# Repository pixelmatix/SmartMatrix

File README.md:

# SmartMatrix Library for Teensy 3, Teensy 4, and ESP32

SmartMatrix Library is designed to refresh HUB75 LED matrix panels and APA102-compatible addressable LEDs with high quality graphics, using simple Arduino sketches.

<p align="center"><i>128x64 HUB75 Panel Driven with SmartLED Shield for Teensy 4</i></p>

SmartMatrix Library 4 has support for Teensy 4.1, Teensy 4.0, Teensy 3.6, Teensy 3.5, Teensy 3.2/3.1, Teensy 3.0, as well as experimental support for ESP32.

The code to refresh HUB75 panels takes advantage of platform-specific peripherals like DMA, I2S, FlexIO, and once started runs in the background using interrupts. It takes a lot of work to port SmartMatrix Library to a new platform. We're working on an open source solution that will allow a lot more platforms to drive HUB75 panels, [sign up for updates here](https://github.com/pixelmatix/SmartMatrix/issues/131) if you're interested.

The documentation in this README contains the basic information you may need to run your first SmartMatrix Library sketch, but there is more detailed documentation in the [SmartMatrix Wiki](https://github.com/pixelmatix/SmartMatrix/wiki).

## Hardware

SmartMatrix Library runs best on the Teensy 4.0 and 4.1 using the SmartLED Shield for Teensy 4, available from [distributors in the US and China](http://docs.pixelmatix.com/SmartMatrix/shop.html). If you want to use the less powerful but more mature Teensy 3, you can use the SmartLED Shield for Teensy 3, available from [Adafruit](https://www.adafruit.com/product/1902), [SparkFun](http://sparkfun.com/products/15046), [Digi-Key](https://www.digikey.com/product-detail/en/sparkfun-electronics/DEV-15046/1568-1954-ND/9739875), and other distributors around the globe. The shield doesn't require any soldering to get started, besides putting pins on your Teensy board.

<p align="center"><i>SmartLED Shield for Teensy 3 - Photo Courtesy Adafruit</i></p>

There's an [adapter PCB design](https://community.pixelmatix.com/t/teensy-4-0-released/498/32) to upgrade SmartLED Shield for Teensy 3 to work with the Teensy 4.

You can wire up a [bare Teensy 3.x to a HUB75 panel](http://docs.pixelmatix.com/SmartMatrix/shieldref.html#smartled-shield-formerly-smartmatrix-shield-overview-technical-details-manually-connecting-teensy-and-panel), but at a minimum it's recommended to use 5V level shifters to drive the panels with the voltage level they are expecting. There's a recommended circuit with latch chip to use with the Teensy 3 that will reduce the amount of pins used. The Teensy 4 requires an external latch.

The shields are Open Source Hardware, with design files posted in the `/extras/hardware/` directories.

Documentation for the SmartLED Shield Hardware is available here: [SmartMatrix Docs](http://docs.pixelmatix.com/SmartMatrix/shieldref.html)

## Teensy 4

Teensy 4 support was contributed by [Eric Eason](https://github.com/easone)

Teensy 4 APA102 support depends on FlexIO_t4 by KurtE, which is included as a submodule in `src/lib/`. The original FlexIO_t4 library is [on GitHub](https://github.com/KurtE/FlexIO_t4)

## ESP32

The ESP32 platform is supported with SmartMatrix Library 4.0, but not all features are up to par with the Teensy 3/4 ports. For details on the ESP32 port, see the [Wiki][def]

## Changes from SmartMatrix Library 3.x

- Sketches written for SmartMatrix Library 3.x should work with SmartMatrix Library 4.0 with a few changes.
- See MIGRATION.md for details on how to update your SmartMatrix Library 3.x sketches for SmartMatrix Library 4.x
- A lot of files were subtly renamed, just changing the case. If you're trying to use git to check out a commit and get an error like `The following untracked working tree files would be overwritten by checkout`, you may need to use git from the command line and add the `-f` parameter to force checkout (throwaway local modifications), as your git client might think it's overwriting the case-changed files and losing data.

### New Features in SmartMatrix Library 4.0

- Support for Teensy 4 and ESP32
- Support for driving APA102 LEDs on Teensy platforms
- New "GFX" layers rewritten for better efficiency, and using Adafruit_GFX for drawing, fonts, including much larger fonts
- Support for panels with non-standard mapping, e.g. 16x32/4 (MOD4) panels
- See more features in the [SmartMatrix Wiki](https://github.com/pixelmatix/SmartMatrix/wiki)

## HUB75 Panels

HUB75 RGB panels are typically used for LED billboards (e.g. Times Square), making them cost-effective and readily available. They’re much cheaper per-pixel than addressable LEDs, and available in a wide range of pixel pitch (as of now, 2 mm spacing up to 10 mm spacing per LED). They do require an external controller to continually send data to the panels to refresh them line by line, and that’s where the SmartLED Shield and SmartMatrix library come in. Adafruit, Sparkfun, and other distributors carry panels that are known to be compatible with SmartLED Shield and the SmartMatrix library, but most panels on AliExpress and other sources are compatible as well.

The pixel pitch and "RGB" are good search terms on Aliexpress, e.g. "P6 RGB" for a 6 mm pitch RGB HUB75 panel.

<p align="center"><i>HUB75 Panels Ranging from P2 to P10 pitch</i></p>

## Getting Started

To download in Arduino Library form, see [Releases](https://github.com/pixelmatix/SmartMatrix/releases) on GitHub, or use Arduino Library Manager.

### Software and Teensy Setup

This documentation assumes you have a general knowledge of the Teensy 3 or Teensy 4, how to use the Arduino IDE, and the Teensyduino addon. If you need an overview of any of those tools, please use these references:

- [PJRC - Teensyduino](http://www.pjrc.com/teensy/teensyduino.html)
- [Arduino - Getting Started with Arduino](http://arduino.cc/en/Guide/HomePage)
- For general Teensy support, not related to the SmartMatrix Shield or SmartMatrix Library, post a question at the [PJRC Forum](http://forum.pjrc.com/forums/3-Technical-Support-amp-Questions)

Make sure you have a supported version of the Arduino IDE and Teensyduino add-on installed.

- [Arduino IDE](http://arduino.cc/en/main/software) - version 1.6.5 or later recommended
- [Teensyduino](http://www.pjrc.com/teensy/td_download.html) - use the latest version

Before continuing, use the blink example in the Arduino IDE to verify you can compile and run a sketch on your Teensy 3.1/3.2.

Download the latest version of the SmartMatrix Library, or install it from Arduino Library Manager:  
[SmartMatrix Releases - GitHub](https://github.com/pixelmatix/SmartMatrix/releases)

Note: "SmartMatrix" Library used to be listed in Arduino Library Manager under "SmartMatrix3". You may need to look for the library in Arduino Library Manager or your libraries folder under either "SmartMatrix" or "SmartMatrix3" as we transition to the new name.

If you're not using Arduino Library Manager, you need to import the library into Arduino, see instructions from Arduino here:  
[Arduino - Libraries](http://arduino.cc/en/Guide/Libraries)

Some of the examples depend on other libraries, which you can download separately, or install from Arduino Library Manager. See "External Libraries" below.

Start with the FeatureDemo Example project, included with the library. From the Arduino File menu, choose Examples, SmartMatrix3 (or SmartMatrix), then FeatureDemo.

Find the section at the top with the note `// uncomment one line to select your MatrixHardware configuration`, and uncomment the file appropriate for your hardware.

You should already have most of the correct Arduino settings to load the FeatureDemo sketch on your Teensy, from running the blink example earlier. For Teensy 3: under Tools, CPU Speed, make sure either 48 MHz or 96MHz (overclock) is selected. (Some libraries are not compatible with the 72MHz CPU). For Teensy 4, use the default CPU speed.

The examples are configured to run on a 32x32-pixel panel. If your resolution is different, adjust the `kMatrixWidth` and `kMatrixHeight` variables at the top of the sketch. You may also need to change `kPanelType`. Some common kPanelType settings:

- 32-pixel high panels, e.g. 32x32, 64x32: `SM_PANELTYPE_HUB75_32ROW_MOD16SCAN`
- 16-pixel high panels, e.g. 32x16: `SMARTMATRIX_HUB75_16ROW_MOD8SCAN`
- 64-pixel high panels, e.g. 64x64, 128x64: `SM_PANELTYPE_HUB75_64ROW_MOD32SCAN`
- For other less common panels, see more details in `MatrixCommonHub75.h` and [the wiki]https://github.com/pixelmatix/SmartMatrix/wiki)

You can chain several panels together to create a wider or taller display than one panel would allow. Set `kMatrixWidth` and `kMatrixHeight` to the overall width and height of your display. If your display is more than one panel high, set `kMatrixOptions` to how you tiled your panels:

- Panel Order - By default, the first panel of each row starts on the same side, so you need a long ribbon cable to go from the last panel of the previous row to the first panel of the next row. `SM_HUB75_OPTIONS_C_SHAPE_STACKING` inverts the panel on each row to minimize the length of the cable going from the last panel of each row the first panel of the other row.
  - Note `SM_HUB75_OPTIONS_C_SHAPE_STACKING` isn't compatible with panels that require the Multi Row Refresh Mapping feature (if your `kPanelType` value includes the column size, it likely requires Multi Row Refresh Mapping, e.g. `SM_PANELTYPE_HUB75_16ROW_32COL_MOD2SCAN`)
- Panel Direction - By default the first panel is on the top row. To stack panels the other way, use `SM_HUB75_OPTIONS_BOTTOM_TO_TOP_STACKING`.
- To set multiple options, use the bitwise-OR operator e.g. for C-shape Bottom-to-top stacking: `const uint8_t kMatrixOptions = (SM_HUB75_OPTIONS_C_SHAPE_STACKING | SM_HUB75_OPTIONS_BOTTOM_TO_TOP_STACKING);`

Note: the stacking direction was reversed in the `teensylc` and `teensy4` branches prior to the release of SmartMatrix Library 4.0. The stacking direction is still reversed for the ESP32 Platform as of SmartMatrix Library 4.0.3, and will be fixed at some point in the future.

Click the Upload button, and the sketch should compile and upload to your Teensy, and start running right away.

You can use the FeatureDemo sketch (or other example sketches) as a way to get started with your own project. Inside `loop()`, find a demo section that is similar to what you want to do with your project, delete the other sections, and save it as as new sketch.

### External Libraries

Some SmartMatrix examples require external libraries to compile. You may already have older versions of these libraries installed in Arduino that may be too old to work with SmartMatrix and the examples. It's usually best to use [Arduino Library Manager](https://learn.adafruit.com/adafruit-all-about-arduino-libraries-install-use) and get the latest version of the library.

Installing Arduino libraries from GitHub has a couple pitfalls. [This Adafruit tutorial](https://learn.adafruit.com/adafruit-all-about-arduino-libraries-install-use/) explains the basics of installing libraries and how to avoid the pitfalls.

**GifDecoder and AnimatedGIF**

There are two libraries needed for the `AnimatedGifs` example. Both can be installed from Arduino Library Manager, or you can manually install from GitHub.

[GifDecoder](https://github.com/pixelmatix/GifDecoder/releases)

[AnimatedGIF](https://github.com/bitbank2/AnimatedGIF/releases)

**Adafruit_GFX**

You can optionally use Adafruit_GFX with SmartMatrix Library. The new "GFX" layers in SmartMatrix Library are much more efficient, and allow for using large fonts for both static display or scrolling across the screen.

Install Adafruit_GFX using Arduino Library Manager or manually [from GitHub](https://github.com/adafruit/Adafruit-GFX-Library/releases)

**FastLED**

If you're having trouble compiling sketches that use FastLED and are getting errors that refer to FastLED.h, try compiling the `FastLED_Functions` example first, which will help narrow down the issue. Also make sure you are using FastLED 3.1 or later.

This error means the FastLED library isn't installed (correctly):  
`fatal error: FastLED.h: No such file or directory`

The FastLED version included with Teensyduino may lag behind the latest. It's better to install FastLED manually using the latest version [available from GitHub](https://github.com/FastLED/FastLED/releases), or using Arduino Library Manager. If you see any of these errors, you likely have an older version of FastLED installed:  
`no known conversion for argument 4 from 'CRGB' to 'const rgb24&'`  
`error: 'inoise8' was not declared in this scope`

This can be tricky to track down as Teensyduino installs libraries into your Arduino application directory, which might not be in your Arduino sketchbook. Look at the `ResolveLibrary` messages you get when compiling to make sure that the version of library you want is being used.

You can manually install the latest version of FastLED (3.x or higher) from the FastLED releases page:
https://github.com/FastLED/FastLED/releases

**Teensy Audio Library**

The SpectrumAnalyzer sketches require the [Teensy Audio Library](http://www.pjrc.com/teensy/td_libs_Audio.html), which is included in Teensyduino. If you have trouble compiling, first make sure you can compile the `FastLED_Functions` example, as FastLED 3.x is also a requirement for this sketch. If you're missing the Audio library, the best way to install is by running the Teensyduino installer. Make sure the "Audio" library is checked during the install.

## Troubleshooting

If you need help, the best place to ask for help, or look for others who may have worked through the same issue, is the [SmartMatrix Community](https://community.pixelmatix.com). Please don't post troubleshooting requests here on GitHub.

If you've found a bug with the code, or want to suggest an improvement, feel free to submit a GitHub Issue or Pull Request.

## Supporting SmartMatrix Library Development

A lot of work went into writing SmartMatrix Library, designing the shields, and releasing them as Open Source Hardware. There are real costs in maintaining the documentation and community forum. If they are useful to you and you'd like to say thank you, you can make a [donation via PayPal](https://www.paypal.com/cgi-bin/webscr?cmd=_s-xclick&hosted_button_id=56RA5NKYXHCLJ&source=https://github.com/pixelmatix/SmartMatrix). Thank you!

[def]: https://github.com/pixelmatix/SmartMatrix/wiki/ESP32-Wiring

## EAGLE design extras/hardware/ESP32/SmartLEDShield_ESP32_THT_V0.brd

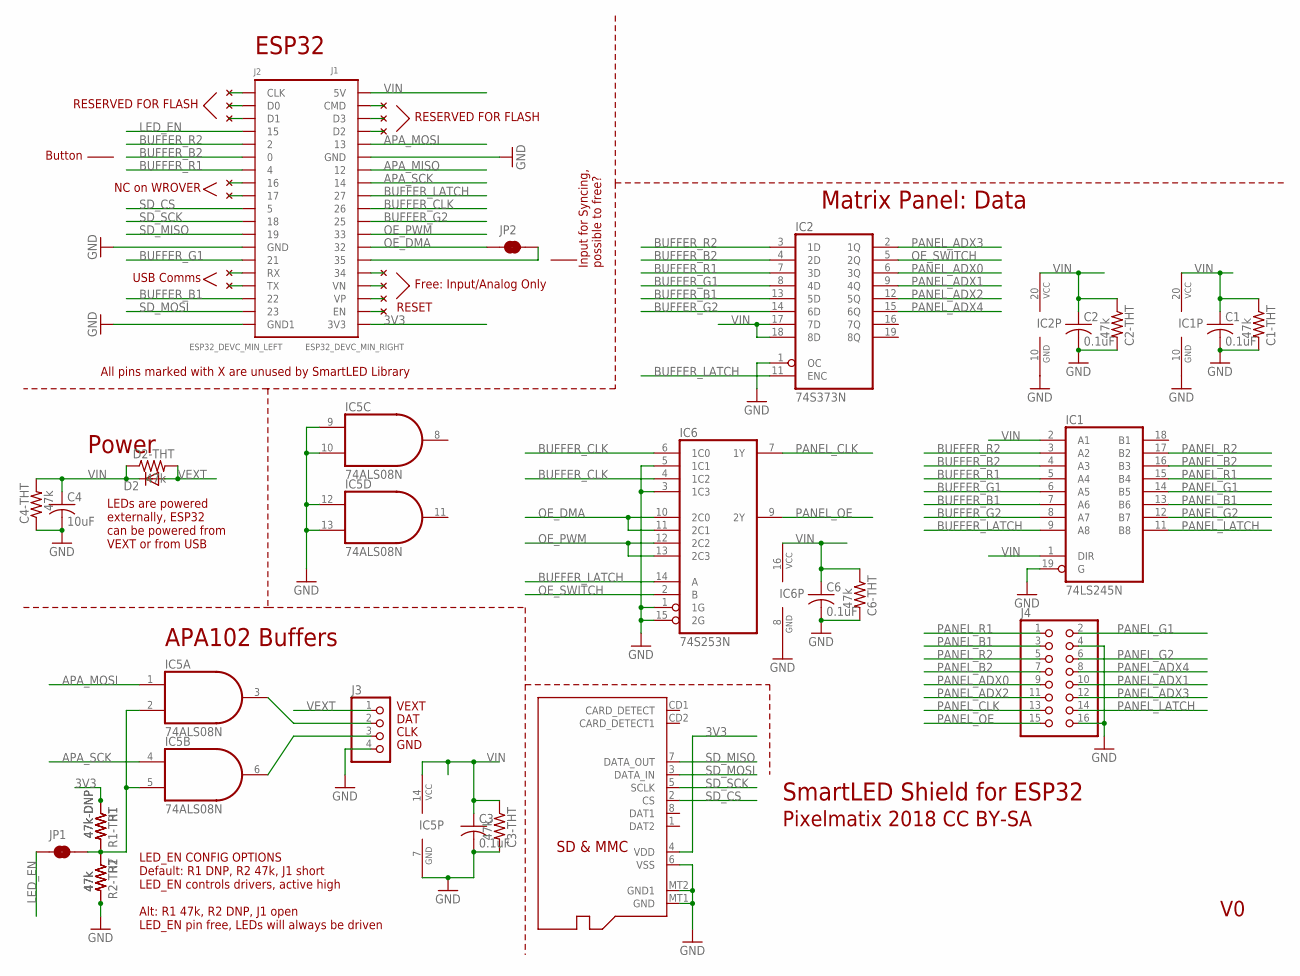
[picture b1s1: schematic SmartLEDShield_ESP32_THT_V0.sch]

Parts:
C1, C2, C3, C6: 0.1uF; C0603; PARTNO CAP CER 0.1UF 10V 10% X7R 0805
C1-THT, C2-THT, C3-THT, C4-THT, C6-THT: 47k; 0204/7
C4: 10uF; C0805; PARTNO CAP CER 0.1UF 10V 10% X7R 0805
D2: MBR1020VL; SOD123-FL
D2-THT: 47k; 0204/7
IC1: 74LS245N; DIL20
IC2: 74S373N; DIL20
IC5: 74ALS08N; DIL14
IC6: 74S253N; DIL16
J1: ESP32_DEVC_MIN_RIGHT; ESP32_DEVC_DUAL_HEADER_BOT_MOUNT_RIGHT
J2: ESP32_DEVC_MIN_LEFT; ESP32_DEVC_DUAL_HEADER_BOT_MOUNT_LEFT
J3: PINHD-1X04_2.54-S; 1X04-S
J4: PINHD-2X08_SMARTMATRIX_SSMTHT; SMARTMATRIX_SSMTHT
J6: MICROSD; PARTNO 101-00660-68-6
JP1, JP2: JUMPER-SMT_2_NC_TRACE_NO-SILK; SMT-JUMPER_2_NC_TRACE_NO-SILK
R1: 47k-DNP; R0603
R1-THT: 47k-DNP; 0204/7
R2: 47k; R0603
R2-THT: 47k; 0204/7

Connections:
3V3: J1.3V3A (3V3), J1.3V3B (3V3), J6.4 (VDD), R1.1, R1-THT.1
APA_MISO: J1.12A (12), J1.12B (12)
APA_MOSI: IC5.1 (I0), J1.13A_A (13), J1.13B_B (13)
APA_SCK: IC5.4 (I0), J1.14A_A (14), J1.14B_B (14)
BUFFER_B1: IC1.7 (A6), IC2.13 (5D), J2.22A (22), J2.22B (22)
BUFFER_B2: IC1.4 (A3), IC2.4 (2D), J2.0A (0), J2.0B (0)
BUFFER_CLK: IC6.4 (1C2), IC6.6 (1C0), J1.26A (26), J1.26B (26)
BUFFER_G1: IC1.6 (A5), IC2.8 (4D), J2.21A (21), J2.21B (21)
BUFFER_G2: IC1.8 (A7), IC2.14 (6D), J1.25A (25), J1.25B (25)
BUFFER_LATCH: IC1.9 (A8), IC2.11 (ENC), IC6.14 (A), J1.27A (27), J1.27B (27)
BUFFER_R1: IC1.5 (A4), IC2.7 (3D), J2.4A (4), J2.4B (4)
BUFFER_R2: IC1.3 (A2), IC2.3 (1D), J2.2A (2), J2.2B (2)
CLK1: IC5.6 (O), J3.3
DAT1: IC5.3 (O), J3.2
GND: C1.2, C1-THT.2, C2.2, C2-THT.2, C3.2, C3-THT.2, C4.2, C4-THT.1, C6.2, C6-THT.2, IC1.10 (GND), IC1.19 (G), IC2.1 (OC), IC2.10 (GND), IC5.7 (GND), IC5.9 (I0), IC5.10 (I1), IC5.12 (I0), IC5.13 (I1), IC6.1 (1G), IC6.3 (1C3), IC6.5 (1C1), IC6.8 (GND), IC6.15 (2G), J1.GNDA (GND), J1.GNDB (GND), J2.GND1A (GND1), J2.GND1B (GND1), J2.GNDA (GND), J2.GNDB (GND), J3.4, J4.4, J4.16, J6.6 (VSS), J6.MT1 (GND), J6.MT2 (GND1), R2.2, R2-THT.2
LED_EN: J2.15A_A (15), J2.15B_B (15), JP1.1
unnamed: J1.35A (35), J1.35B (35), JP2.2
unnamed: J1.CMD_A (CMD), J1.CMD_B (CMD)
unnamed: J1.D3_A (D3), J1.D3_B (D3)
unnamed: IC5.2 (I1), IC5.5 (I1), JP1.2, R1.2, R1-THT.2, R2.1, R2-THT.1
unnamed: J1.D2A (D2), J1.D2B (D2)
unnamed: J2.CLKA (CLK), J2.CLKB (CLK)
unnamed: J2.D0A (D0), J2.D0B (D0)
unnamed: J2.D1A (D1), J2.D1B (D1)
unnamed: J1.VNA (VN), J1.VNB (VN)
unnamed: J1.VPA (VP), J1.VPB (VP)
unnamed: J1.34A (34), J1.34B (34)
unnamed: J1.ENA (EN), J1.ENB (EN)
unnamed: J2.TXA (TX), J2.TXB (TX)
unnamed: J2.RXA (RX), J2.RXB (RX)
unnamed: J2.17A_A (17), J2.17B_B (17)
unnamed: J2.16A_A (16), J2.16_B (16)
OE_DMA: IC6.10 (2C0), IC6.11 (2C1), J1.32A (32), J1.32B (32), JP2.1
OE_PWM: IC6.12 (2C2), IC6.13 (2C3), J1.33A (33), J1.33B (33)
OE_SWITCH: IC2.5 (2Q), IC6.2 (B)
PANEL_ADX0: IC2.6 (3Q), J4.9
PANEL_ADX1: IC2.9 (4Q), J4.10
PANEL_ADX2: IC2.12 (5Q), J4.11
PANEL_ADX3: IC2.2 (1Q), J4.12
PANEL_ADX4: IC2.15 (6Q), J4.8
PANEL_B1: IC1.13 (B6), J4.3
PANEL_B2: IC1.16 (B3), J4.7
PANEL_CLK: IC6.7 (1Y), J4.13
PANEL_G1: IC1.14 (B5), J4.2
PANEL_G2: IC1.12 (B7), J4.6
PANEL_LATCH: IC1.11 (B8), J4.14
PANEL_OE: IC6.9 (2Y), J4.15
PANEL_R1: IC1.15 (B4), J4.1
PANEL_R2: IC1.17 (B2), J4.5
SD_CS: J2.5A (5), J2.5B (5), J6.2 (CS)
SD_MISO: J2.19A_A (19), J2.19B_B (19), J6.7 (DATA_OUT)
SD_MOSI: J2.23A (23), J2.23B (23), J6.3 (DATA_IN)
SD_SCK: J2.18A_A (18), J2.18B_B (18), J6.5 (SCLK)
VEXT: D2.A, D2-THT.2, J3.1
VIN: C1.1, C1-THT.1, C2.1, C2-THT.1, C3.1, C3-THT.1, C4.1, C4-THT.2, C6.1, C6-THT.1, D2.C, D2-THT.1, IC1.1 (DIR), IC1.2 (A1), IC1.20 (VCC), IC2.17 (7D), IC2.18 (8D), IC2.20 (VCC), IC5.14 (VCC), IC6.16 (VCC), J1.5V_A (5V), J1.5V_B (5V)

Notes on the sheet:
SmartLED Shield for ESP32
Pixelmatix 2018 CC BY-SA
ESP32
Matrix Panel: Data
VEXT
CLK
GND
DAT
Power
LEDs are powered externally, ESP32 can be powered from VEXT or from USB
LED_EN CONFIG OPTIONS Default: R1 DNP, R2 47k, J1 short LED_EN controls drivers, active high Alt: R1 47k, R2 DNP, J1 open LED_EN pin free, LEDs will always be driven
APA102 Buffers
All pins marked with X are unused by SmartLED Library
RESERVED FOR FLASH
Free: Input/Analog Only
Input for Syncing, possible to free?
RESET
USB Comms
NC on WROVER
Button

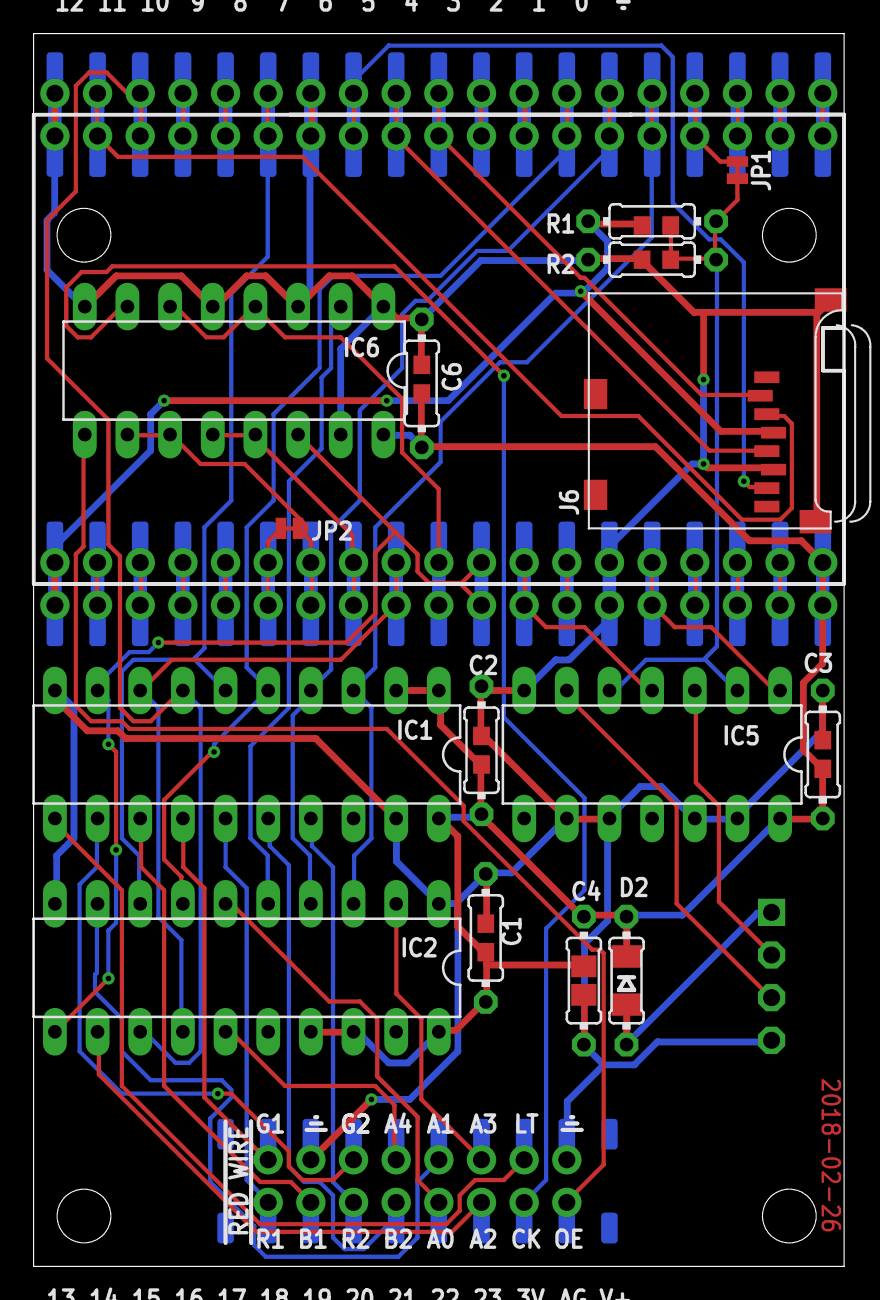
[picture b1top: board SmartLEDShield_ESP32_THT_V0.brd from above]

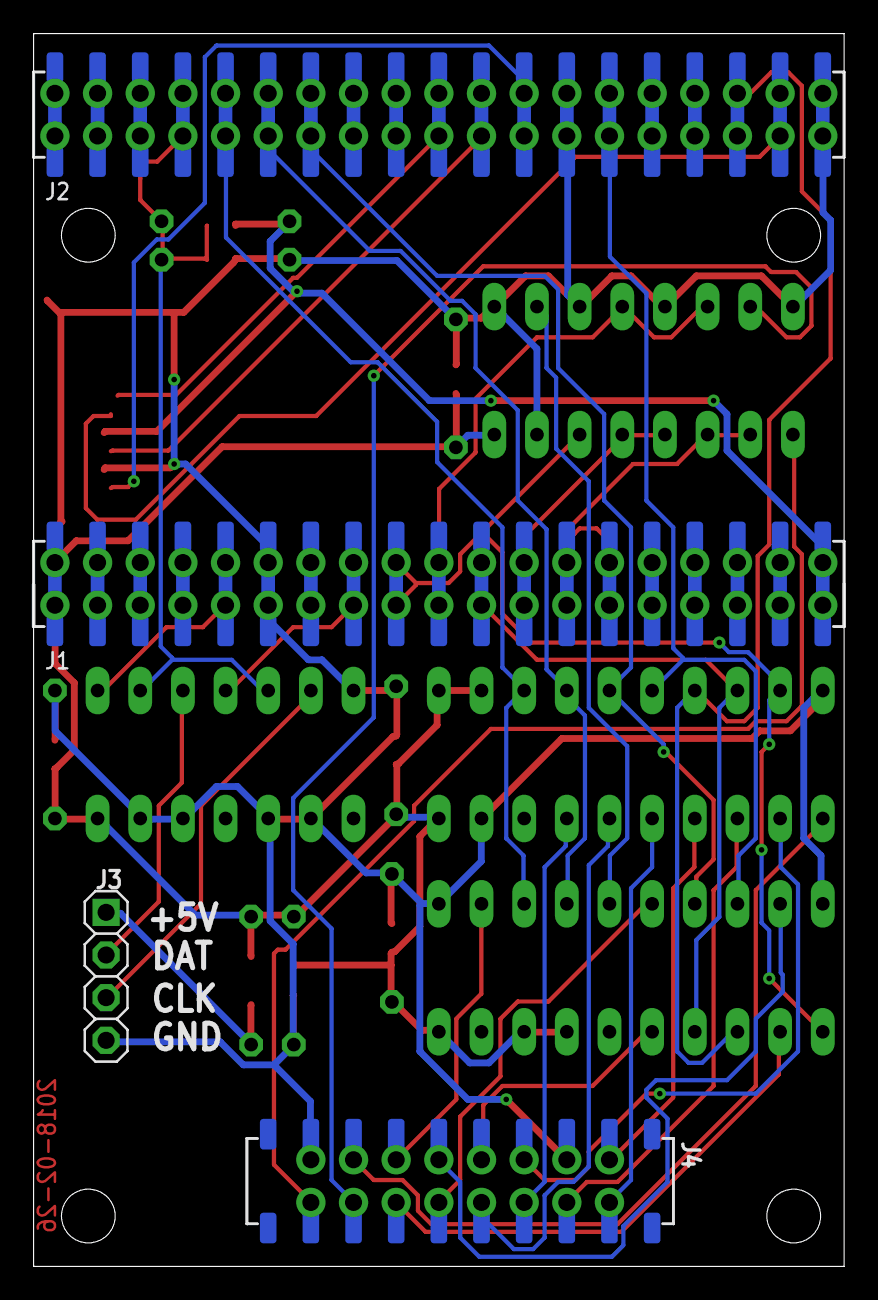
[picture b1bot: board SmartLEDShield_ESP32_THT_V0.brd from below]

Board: 2 copper layers, 48.3 x 73.4 mm, 31 parts (4 on the bottom side), 55 nets.

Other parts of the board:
H1, H3, H6, H9: STAND-OFFSTAND-OFF-3MM; STAND-OFF-3MM

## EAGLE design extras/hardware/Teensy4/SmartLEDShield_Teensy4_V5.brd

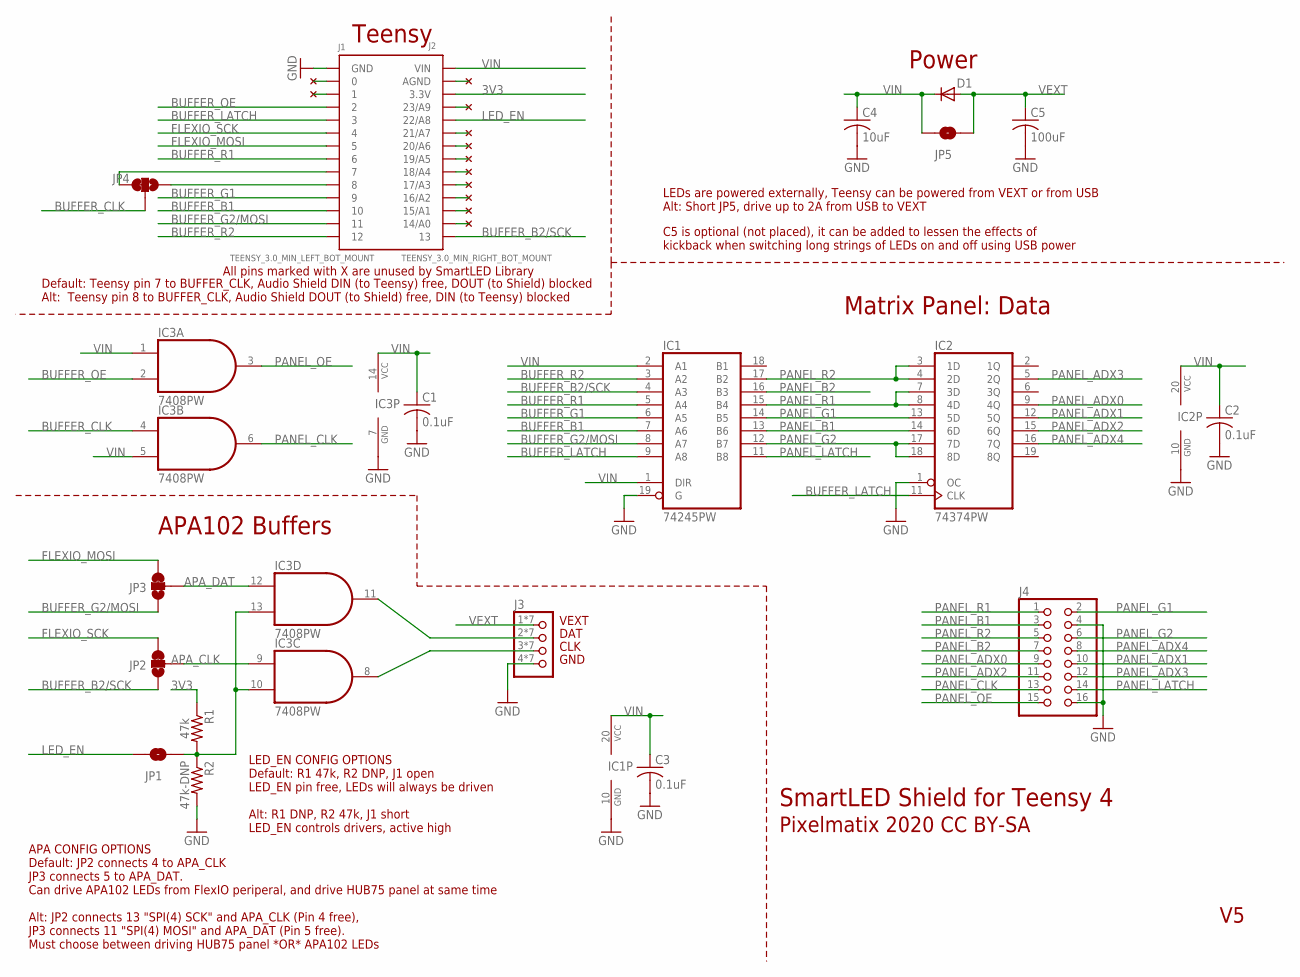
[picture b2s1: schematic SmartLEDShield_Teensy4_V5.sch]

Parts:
C1, C2, C3: 0.1uF; C0603; PARTNO CAP CER 0.1UF 10V 10% X7R 0805
C4: 10uF; C0805; PARTNO CAP CER 0.1UF 10V 10% X7R 0805
C5: 100uF; C1206; PARTNO CAP CER 0.1UF 10V 10% X7R 0805
D1: MBR0520LT; SOD123
IC1: 74245PW; TSSOP-20
IC2: 74374PW; TSSOP-20
IC3: 7408PW; TSSOP14
J1: TEENSY_3.0_MIN_LEFT_BOT_MOUNT; TEENSY_DUAL_HEADER_BOT_MOUNT_LEFT
J2: TEENSY_3.0_MIN_RIGHT_BOT_MOUNT; TEENSY_DUAL_HEADER_BOT_MOUNT_RIGHT
J3: PINHD-1X04_WIREPADS_NARROW; 1X04SMDWIRES_NARROW
J4: PINHD-2X08_SMARTMATRIX_SSMTHT; SMARTMATRIX_SSMTHT
JP1, JP5: JUMPER-SMT_2_NO_SILK; SMT-JUMPER_2_NO_SILK
JP2, JP3: JUMPER-SMT_3_1-NC_TRACE_SILK; SMT-JUMPER_3_1-NC_TRACE_SILK
JP4: JUMPER-SMT_3_1-NC_TRACE_NO-SILK; SMT-JUMPER_3_1-NC_TRACE_NO-SILK
R1: 47k; R0603
R2: 47k-DNP; R0603

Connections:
3V3: J2.3V3_A (3.3V), J2.3V3_B (3.3V), R1.1
APA_CLK: IC3.9 (I0), JP2.2
APA_DAT: IC3.12 (I0), JP3.2
BUFFER_B1: IC1.7 (A6), J1.10A (10), J1.10B (10)
BUFFER_B2/SCK: IC1.4 (A3), J2.13A (13), J2.13B (13), JP2.1
BUFFER_CLK: IC3.4 (I0), JP4.2
BUFFER_G1: IC1.6 (A5), J1.9A (9), J1.9B (9)
BUFFER_G2/MOSI: IC1.8 (A7), J1.11A (11), J1.11B (11), JP3.1
BUFFER_LATCH: IC1.9 (A8), IC2.11 (CLK), J1.3A (3), J1.3B (3)
BUFFER_OE: IC3.2 (I1), J1.2A (2), J1.2B (2)
BUFFER_R1: IC1.5 (A4), J1.6A (6), J1.6B (6)
BUFFER_R2: IC1.3 (A2), J1.12A (12), J1.12B (12)
CLK1: IC3.8 (O), J3.3, J3.3-1 (3), J3.3-2 (3), J3.3-3 (3), J3.3-4 (3), J3.3-5 (3), J3.3-6 (3)
DAT1: IC3.11 (O), J3.2, J3.2-1 (2), J3.2-2 (2), J3.2-3 (2), J3.2-4 (2), J3.2-5 (2), J3.2-6 (2)
FLEXIO_MOSI: J1.5A (5), J1.5B (5), JP3.3
FLEXIO_SCK: J1.4A (4), J1.4B (4), JP2.3
GND: C1.2, C2.2, C3.2, C4.2, C5.2, IC1.10 (GND), IC1.19 (G), IC2.1 (OC), IC2.10 (GND), IC3.7 (GND), J1.GNDA (GND), J1.GNDB (GND), J3.4, J3.4-1 (4), J3.4-2 (4), J3.4-3 (4), J3.4-4 (4), J3.4-5 (4), J3.4-6 (4), J4.4, J4.16, R2.2
LED_EN: J2.22A (22/A8), J2.22B (22/A8), JP1.1
unnamed: J1.0A (0), J1.0B (0)
unnamed: J2.21A (21/A7), J2.21B (21/A7)
unnamed: J2.20A (20/A6), J2.20B (20/A6)
unnamed: IC3.10 (I1), IC3.13 (I1), JP1.2, R1.2, R2.1
unnamed: J1.1A (1), J1.1B (1)
unnamed: J2.AGND_A (AGND), J2.AGND_B (AGND)
unnamed: J2.19A (19/A5), J2.19B (19/A5)
unnamed: J2.18A (18/A4), J2.18B (18/A4)
unnamed: J2.23A (23/A9), J2.23B (23/A9)
unnamed: J2.16A (16/A2), J2.16B (16/A2)
unnamed: J2.15A (15/A1), J2.15B (15/A1)
unnamed: J2.17A (17/A3), J2.17B (17/A3)
unnamed: J2.14A (14/A0), J2.14B (14/A0)
unnamed: J1.7A (7), J1.7B (7), JP4.3
unnamed: J1.8A (8), J1.8B (8), JP4.1
PANEL_ADX0: IC2.9 (4Q), J4.9
PANEL_ADX1: IC2.12 (5Q), J4.10
PANEL_ADX2: IC2.15 (6Q), J4.11
PANEL_ADX3: IC2.5 (2Q), J4.12
PANEL_ADX4: IC2.16 (7Q), J4.8
PANEL_B1: IC1.13 (B6), IC2.14 (6D), J4.3
PANEL_B2: IC1.16 (B3), J4.7
PANEL_CLK: IC3.6 (O), J4.13
PANEL_G1: IC1.14 (B5), IC2.13 (5D), J4.2
PANEL_G2: IC1.12 (B7), IC2.17 (7D), IC2.18 (8D), J4.6
PANEL_LATCH: IC1.11 (B8), J4.14
PANEL_OE: IC3.3 (O), J4.15
PANEL_R1: IC1.15 (B4), IC2.7 (3D), IC2.8 (4D), J4.1
PANEL_R2: IC1.17 (B2), IC2.3 (1D), IC2.4 (2D), J4.5
VEXT: C5.1, D1.A, J3.1, J3.1-1 (1), J3.1-2 (1), J3.1-3 (1), J3.1-4 (1), J3.1-5 (1), J3.1-6 (1), JP5.2
VIN: C1.1, C2.1, C3.1, C4.1, D1.C, IC1.1 (DIR), IC1.2 (A1), IC1.20 (VCC), IC2.20 (VCC), IC3.1 (I0), IC3.5 (I1), IC3.14 (VCC), J2.VIN_A (VIN), J2.VIN_B (VIN), JP5.1

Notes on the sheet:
SmartLED Shield for Teensy 4
Pixelmatix 2020 CC BY-SA
Teensy
Matrix Panel: Data
VEXT
CLK
GND
DAT
Power
C5 is optional (not placed), it can be added to lessen the effects of kickback when switching long strings of LEDs on and off using USB power
LEDs are powered externally, Teensy can be powered from VEXT or from USB Alt: Short JP5, drive up to 2A from USB to VEXT
LED_EN CONFIG OPTIONS Default: R1 47k, R2 DNP, J1 open LED_EN pin free, LEDs will always be driven Alt: R1 DNP, R2 47k, J1 short LED_EN controls drivers, active high
APA102 Buffers
APA CONFIG OPTIONS Default: JP2 connects 4 to APA_CLK JP3 connects 5 to APA_DAT. Can drive APA102 LEDs from FlexIO periperal, and drive HUB75 panel at same time Alt: JP2 connects 13 "SPI(4) SCK" and APA_CLK (Pin 4 free), JP3 connects 11 "SPI(4) MOSI" and APA_DAT (Pin 5 free). Must choose between dr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
All pins marked with X are unused by SmartLED Library
Default: Teensy pin 7 to BUFFER_CLK, Audio Shield DIN (to Teensy) free, DOUT (to Shield) blocked Alt: Teensy pin 8 to BUFFER_CLK, Audio Shield DOUT (to Shield) free, DIN (to Teensy) blocked

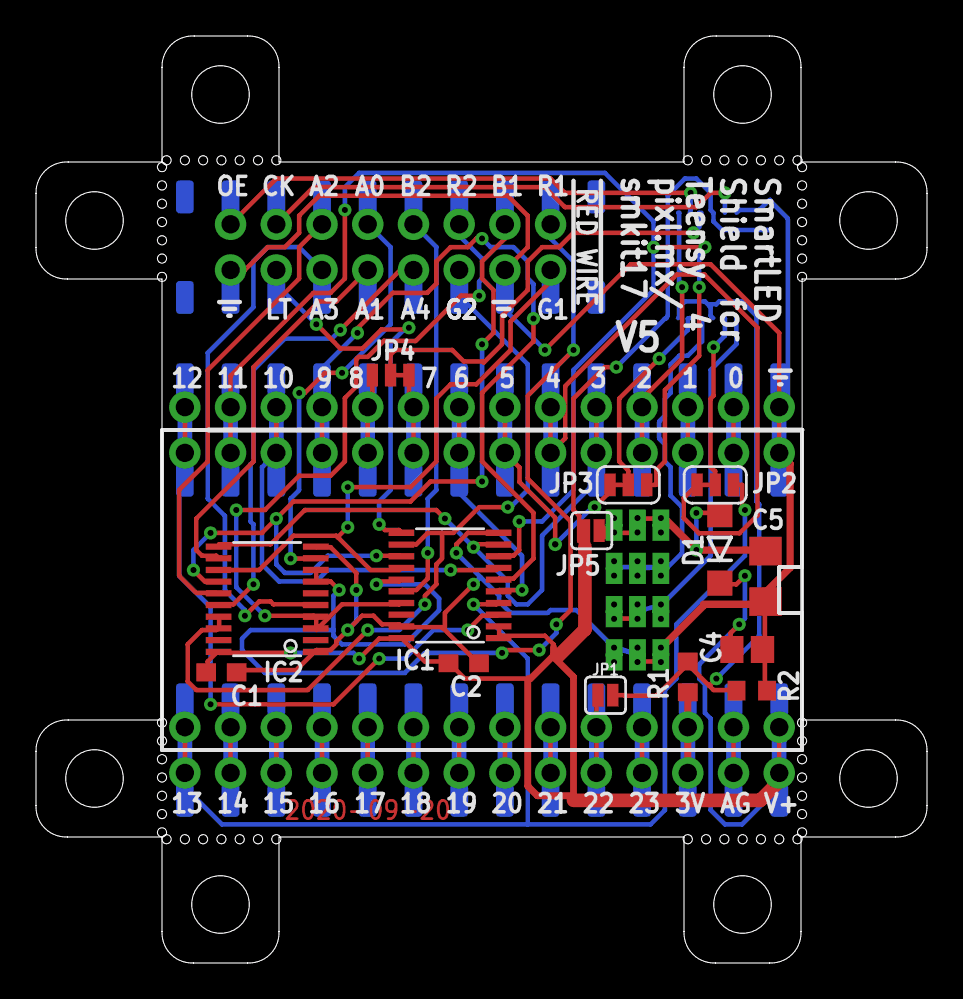
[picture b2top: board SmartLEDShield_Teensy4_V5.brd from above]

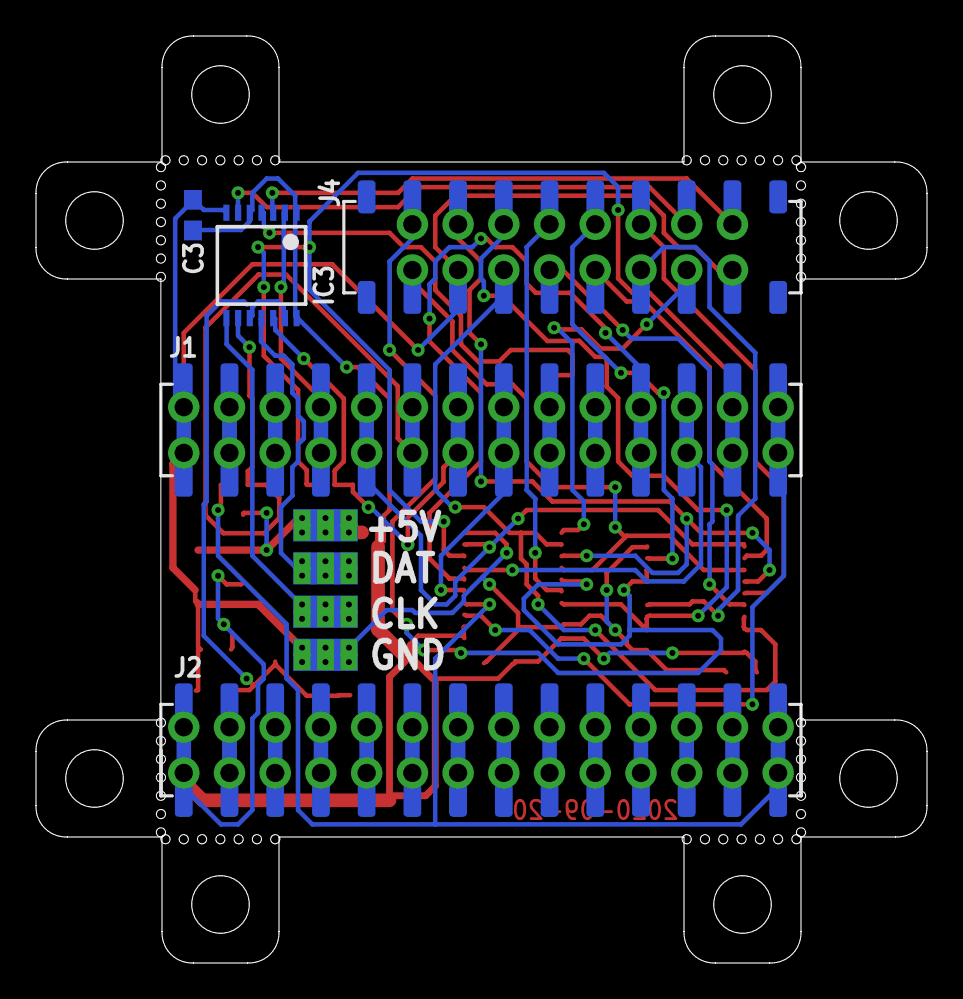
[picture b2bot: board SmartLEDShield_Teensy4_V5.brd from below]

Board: 2 copper layers, 49.5 x 51.5 mm, 28 parts (6 on the bottom side), 49 nets.

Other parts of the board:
H1, H2, H3, H4, H5, H6, H7, H9: STAND-OFFSTAND-OFF-3MM; STAND-OFF-3MM

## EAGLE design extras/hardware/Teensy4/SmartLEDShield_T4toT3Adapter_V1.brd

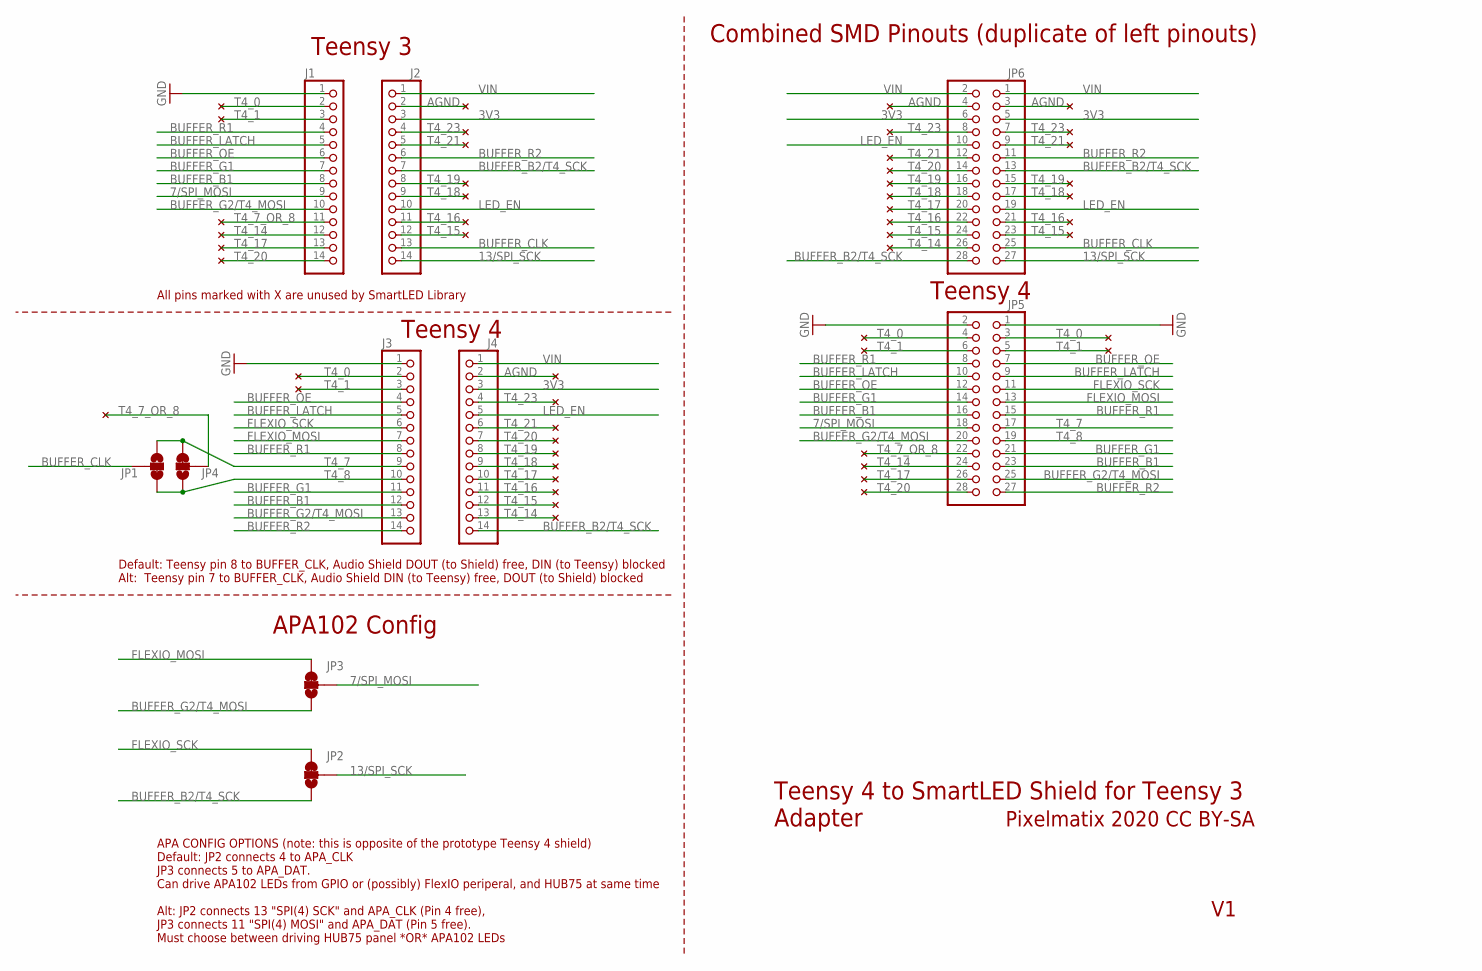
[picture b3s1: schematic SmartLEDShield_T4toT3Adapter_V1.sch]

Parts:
J1, J2, J3, J4: PINHD-1X14_2.54-S; 1X14-S
JP1, JP2, JP3, JP4: JUMPER-SMT_3_1-NC_TRACE_SILK; SMT-JUMPER_3_1-NC_TRACE_SILK
JP5, JP6: PINHD-2X14_2.54-SMD; 2X14SMD

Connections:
3V3: J2.3, J4.3, JP6.5, JP6.6
7/SPI_MOSI: J1.9, JP3.2, JP5.18
13/SPI_SCK: J2.14, JP2.2, JP6.27
AGND: J2.2, J4.2, JP6.3, JP6.4
BUFFER_B1: J1.8, J3.12, JP5.16, JP5.23
BUFFER_B2/T4_SCK: J2.7, J4.14, JP2.1, JP6.13, JP6.28
BUFFER_CLK: J2.13, JP1.2, JP6.25
BUFFER_G1: J1.7, J3.11, JP5.14, JP5.21
BUFFER_G2/T4_MOSI: J1.10, J3.13, JP3.1, JP5.20, JP5.25
BUFFER_LATCH: J1.5, J3.5, JP5.9, JP5.10
BUFFER_OE: J1.6, J3.4, JP5.7, JP5.12
BUFFER_R1: J1.4, J3.8, JP5.8, JP5.15
BUFFER_R2: J2.6, J3.14, JP5.27, JP6.11
FLEXIO_MOSI: J3.7, JP3.3, JP5.13
FLEXIO_SCK: J3.6, JP2.3, JP5.11
GND: J1.1, J3.1, JP5.1, JP5.2
LED_EN: J2.10, J4.5, JP6.10, JP6.19
T4_0: J1.2, J3.2, JP5.3, JP5.4
T4_1: J1.3, J3.3, JP5.5, JP5.6
T4_7: J3.9, JP1.1, JP4.3, JP5.17
T4_7_OR_8: J1.11, JP4.2, JP5.22
T4_8: J3.10, JP1.3, JP4.1, JP5.19
T4_14: J1.12, J4.13, JP5.24, JP6.26
T4_15: J2.12, J4.12, JP6.23, JP6.24
T4_16: J2.11, J4.11, JP6.21, JP6.22
T4_17: J1.13, J4.10, JP5.26, JP6.20
T4_18: J2.9, J4.9, JP6.17, JP6.18
T4_19: J2.8, J4.8, JP6.15, JP6.16
T4_20: J1.14, J4.7, JP5.28, JP6.14
T4_21: J2.5, J4.6, JP6.9, JP6.12
T4_23: J2.4, J4.4, JP6.7, JP6.8
VIN: J2.1, J4.1, JP6.1, JP6.2

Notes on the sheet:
Teensy 4 to SmartLED Shield for Teensy 3 Adapter
Pixelmatix 2020 CC BY-SA
Teensy 3
All pins marked with X are unused by SmartLED Library
Teensy 4
APA CONFIG OPTIONS (note: this is opposite of the prototype Teensy 4 shield) Default: JP2 connects 4 to APA_CLK JP3 connects 5 to APA_DAT. Can drive APA102 LEDs from GPIO or (possibly) FlexIO periperal, and HUB75 at same time Alt: JP2 connects 13 "SPI(4) SCK" and APA_CLK (Pin 4 free), JP3 connects 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
Default: Teensy pin 8 to BUFFER_CLK, Audio Shield DOUT (to Shield) free, DIN (to Teensy) blocked Alt: Teensy pin 7 to BUFFER_CLK, Audio Shield DIN (to Teensy) free, DOUT (to Shield) blocked
APA102 Config
Combined SMD Pinouts (duplicate of left pinouts)

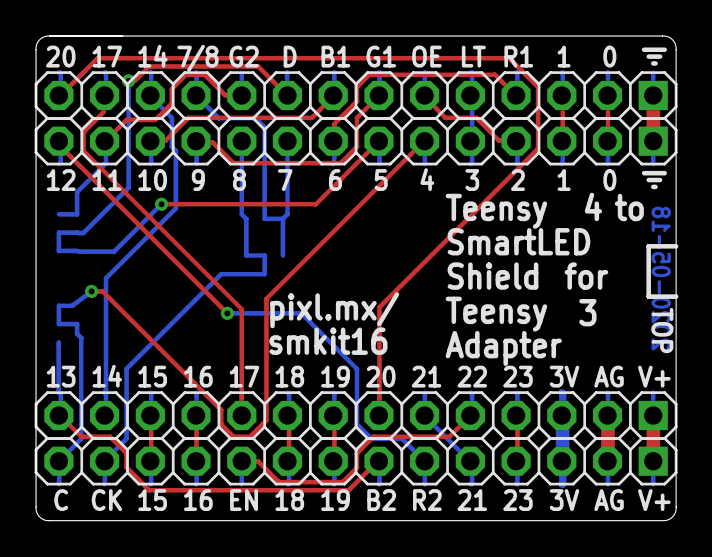
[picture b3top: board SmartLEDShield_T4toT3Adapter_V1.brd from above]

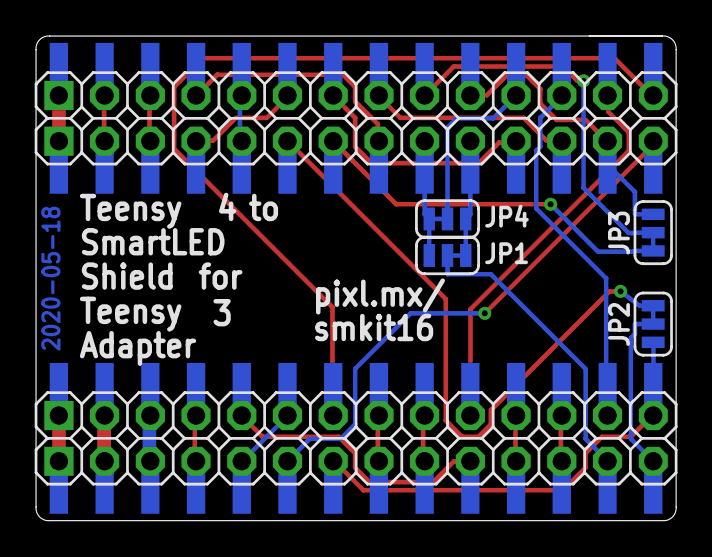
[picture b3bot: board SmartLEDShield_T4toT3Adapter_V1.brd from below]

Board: 2 copper layers, 35.6 x 26.9 mm, 10 parts (6 on the bottom side), 32 nets.

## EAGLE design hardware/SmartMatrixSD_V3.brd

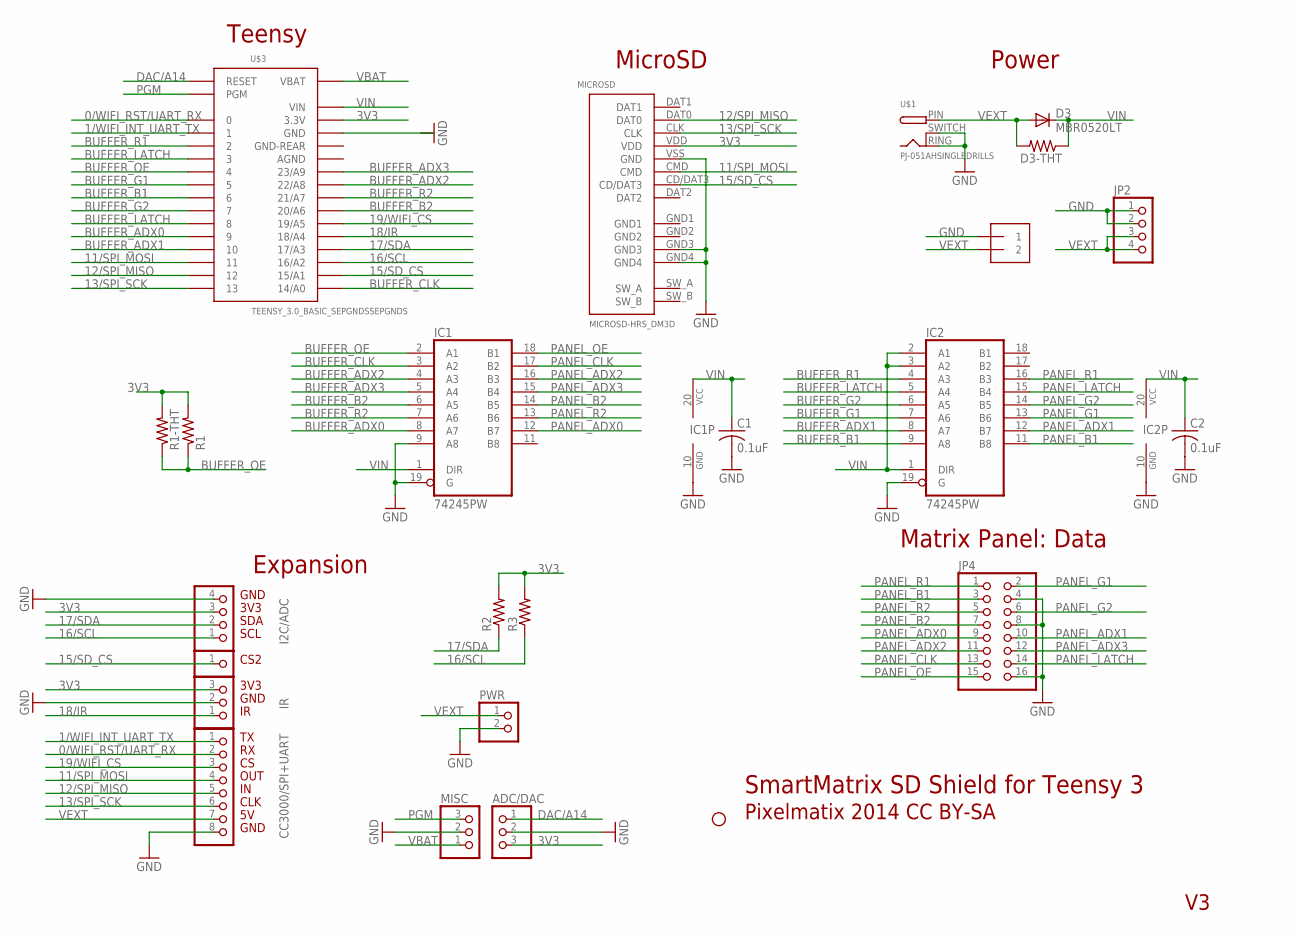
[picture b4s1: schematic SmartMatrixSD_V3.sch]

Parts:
ADC/DAC: PINHD-1X03_2.54-S; 1X03-S
C1, C2: 0.1uF; C0603; PARTNO CAP CER 0.1UF 10V 10% X7R 0805
CC3000/SPI+UART: PINHD-1X08_2.54-S; 1X08-S
CS2: PINHD-1X01_2.54-S; 1X01-S
D3: MBR0520LT; SOD123
D3-THT: R-US_0207/2V; 0207/2V
I2C/ADC: PINHD-1X04_2.54-S; 1X04-S
IC1, IC2: 74245PW; TSSOP-20
IR: PINHD-1X03_2.54-S; 1X03-S
J4: 1X2-5.0; 1X2-5.0MM
JP2: PINHD-1X04_1.56; 1X04-1.56"
JP4: PINHD-2X08_2.54; 2X08
JP5: STAND-OFFSTAND-OFF-3MM; STAND-OFF-3MM
MICROSD: MICROSD-HRS_DM3D; DM3D
MISC: PINHD-1X03_2.54-S; 1X03-S
PWR: PINHD-1X02_2.54-S; 1X02-S
R1: R-US_R0603; R0603
R1-THT: R-US_0207/2V; 0207/2V
R2, R3: R-US_0207/7; 0207/7
U$1: PJ-051AHSINGLEDRILLS; PJ-051AH-SINGLEDRILLS
U$3: TEENSY_3.0_BASIC_SEPGNDSSEPGNDS; TEENSY_3.0_BASIC

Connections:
0/WIFI_RST/UART_RX: CC3000/SPI+UART.2, U$3.0
1/WIFI_INT_UART_TX: CC3000/SPI+UART.1, U$3.1
3V3: ADC/DAC.3, I2C/ADC.3, IR.3, MICROSD.VDD, R1.2, R1-THT.2, R2.2, R3.2, U$3.3.3V, U$3.3.3V1 (3.3V)
11/SPI_MOSI: CC3000/SPI+UART.4, MICROSD.CMD, U$3.11
12/SPI_MISO: CC3000/SPI+UART.5, MICROSD.DAT0, U$3.12
13/SPI_SCK: CC3000/SPI+UART.6, MICROSD.CLK, U$3.13
15/SD_CS: CS2.1, MICROSD.CD/DAT3, U$3.15/A1
16/SCL: I2C/ADC.1, R3.1, U$3.16/A2
17/SDA: I2C/ADC.2, R2.1, U$3.17/A3
18/IR: IR.1, U$3.18/A4
19/WIFI_CS: CC3000/SPI+UART.3, U$3.19/A5
AGND: U$3.AGND
BUFFER_ADX0: IC1.8 (A7), U$3.9
BUFFER_ADX1: IC2.8 (A7), U$3.10
BUFFER_ADX2: IC1.4 (A3), U$3.22/A8
BUFFER_ADX3: IC1.5 (A4), U$3.23/A9
BUFFER_B1: IC2.9 (A8), U$3.6
BUFFER_B2: IC1.6 (A5), U$3.20/A6
BUFFER_CLK: IC1.3 (A2), U$3.14/A0
BUFFER_G1: IC2.7 (A6), U$3.5
BUFFER_G2: IC2.6 (A5), U$3.7
BUFFER_LATCH: IC2.5 (A4), U$3.3, U$3.8
BUFFER_OE: IC1.2 (A1), R1.1, R1-THT.1, U$3.4
BUFFER_R1: IC2.4 (A3), U$3.2
BUFFER_R2: IC1.7 (A6), U$3.21/A7
DAC/A14: ADC/DAC.1, U$3.RESET
GND: ADC/DAC.2, C1.2, C2.2, CC3000/SPI+UART.8, I2C/ADC.4, IC1.9 (A8), IC1.10 (GND), IC1.19 (G), IC2.10 (GND), IC2.19 (G), IR.2, J4.1, JP2.1, JP2.2, JP4.4, JP4.8, JP4.16, MICROSD.GND3, MICROSD.GND4, MICROSD.VSS (GND), MISC.2, PWR.2, U$1.RING (GND), U$1.SWITCH (GNDBREAK), U$3.GND
GND-REAR: U$3.GND1 (GND-REAR)
PANEL_ADX0: IC1.12 (B7), JP4.9
PANEL_ADX1: IC2.12 (B7), JP4.10
PANEL_ADX2: IC1.16 (B3), JP4.11
PANEL_ADX3: IC1.15 (B4), JP4.12
PANEL_B1: IC2.11 (B8), JP4.3
PANEL_B2: IC1.14 (B5), JP4.7
PANEL_CLK: IC1.17 (B2), JP4.13
PANEL_G1: IC2.13 (B6), JP4.2
PANEL_G2: IC2.14 (B5), JP4.6
PANEL_LATCH: IC2.15 (B4), JP4.14
PANEL_OE: IC1.18 (B1), JP4.15
PANEL_R1: IC2.16 (B3), JP4.1
PANEL_R2: IC1.13 (B6), JP4.5
PGM: MISC.3, U$3.PGM
VBAT: MISC.1, U$3.VBAT
VEXT: CC3000/SPI+UART.7, D3.A, D3-THT.2, J4.2, JP2.3, JP2.4, PWR.1, U$1.PIN (PWR)
VIN: C1.1, C2.1, D3.C, D3-THT.1, IC1.1 (DIR), IC1.20 (VCC), IC2.1 (DIR), IC2.2 (A1), IC2.3 (A2), IC2.20 (VCC), U$3.VIN

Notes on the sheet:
SmartMatrix SD Shield for Teensy 3
Pixelmatix 2014 CC BY-SA
Teensy
Power
Matrix Panel: Data
Expansion
MicroSD
GND
3V3
SDA
SCL
CS2
OUT
CLK

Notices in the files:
extras/hardware/ESP32/SmartLEDShield_ESP32_THT_V0.brd:
Pixelmatix 2017 CC BY-SA
hardware/SmartMatrixSD_V3.brd:
Pixelmatix 2015 CC BY-SA
parts and their libraries:
SparkFun-Jumpers: Licensing: Creative Commons ShareAlike 4.0 International - https://creativecommons.org/licenses/by-sa/4.0
